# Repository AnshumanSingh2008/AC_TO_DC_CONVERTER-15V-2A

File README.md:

# 15 V / 2 A Linear DC Power Supply (LM350) - KiCad Design Study

A transformer-based, regulated 15 V / 2 A DC supply designed in KiCad as a learning project. The goal was to recreate a commercial plug-in AC-DC adapter. The design works on paper and passes ERC and DRC, but comparing it with the real adapter showed that a linear supply is the wrong architecture for a compact, low-cost product. This README documents the design and, more importantly, why it was not taken to fabrication.

## Project status

| Item | Status |
|---|---|
| Schematic | Complete, ERC clean |
| PCB layout | Complete, DRC clean |
| Gerbers and drill files | Generated (`fabrication/`) |
| Fabricated and tested | **No. Design only.** |
| Decision | Not fabricated, for cost and size reasons (see below) |

## Specifications

| Parameter | Value |
|---|---|
| Input | 18 V AC from an external 230 V isolating transformer (3 A secondary) |
| Output | 15 V DC, up to 2 A |
| Regulator | LM350 adjustable (TO-220) |
| Rectifier | Bridge of 4 x 1N5408 |
| Bulk filter | 4700 uF / 35 V |
| Board size | 71.1 mm x 63 mm, two layers |
| Connectors | 2 x 5.08 mm screw terminals (AC in, DC out) |

No mains voltage reaches the PCB. Mains connects only to the off-board transformer primary.

## How it works

```
230 V AC -> Transformer (off-board) -> 18 V AC -> J1
   -> Bridge rectifier (D5-D8) -> C1 bulk filter (~24 V DC peak)
   -> C2 input bypass -> U1 LM350 -> C3/C4 -> J2 (15 V out)
```

- **Bridge and C1** convert the 18 V AC to rippled DC of about 22-24 V.
- **U1 (LM350)** holds 1.25 V between its output and ADJ pins. R1 = 120 ohm and R2 = 1.3 kohm set the output: Vout = 1.25 x (1 + R2/R1), about 14.8 V.
- **D1** (output to input) and **D2** (ADJ to output) protect the regulator from capacitor discharge if the input collapses.
- **C2, C3, C4** provide input bypass, output stability and ADJ ripple reduction.
- **R3 + LED** give a power indicator.

## Key design decisions

| Decision | Reason |
|---|---|
| LM350 instead of 7815 | 78xx parts are limited to 1.5 A; 2 A needed an adjustable 3 A part |
| 1N5408 bridge diodes | 3 A rating; 1N4007 (1 A) is too small for 2 A with capacitor-input peaks |
| 18 V AC secondary | Gives enough headroom (about 3 V) above 15 V under load and mains dips |
| Off-board transformer | Keeps mains off the PCB, so no creepage/clearance issues and a safe board to handle |
| 2 mm tracks on power paths | Sized for 2 A on 1 oz copper; thin 0.5 mm tracks on mA-level signal nets |

## Why I did not build it (the learnings)

### 1. The PCB alone was larger than a commercial adapter

The commercial 12 V / 2 A adapter I wanted to match measures about **7.8 cm x 4.7 cm**, including its plastic case and mains pins. My bare PCB measures **7.1 cm x 6.3 cm**, before adding the transformer, heatsink and enclosure.

The reason is architecture, not layout quality:

- The adapter is a **switch-mode power supply (SMPS)**. It rectifies mains directly and switches at tens of kHz, so its transformer is a tiny ferrite part.
- My design is a **linear supply**. It needs a 50 Hz transformer (large and heavy), a 4700 uF bulk capacitor, large 1N5408 diodes, and a heatsink for the regulator.
- The LM350 dissipates roughly (Vin - Vout) x I, about 14 W or more at full load, so the regulator needs a large heatsink and ventilation.

### 2. The transformer alone cost more than the complete adapter

A suitable 18 V / 3 A isolating transformer costs about **Rs 1500**. The finished commercial adapter costs about **Rs 450**. Before counting the PCB, regulator, heatsink, capacitors, fuse and enclosure, the design is already several times more expensive than the product it was meant to replace.

### Conclusion

For a compact, low-cost 12-15 V / 2 A adapter, a linear supply is the wrong choice. A **flyback SMPS** is the right architecture: smaller, cooler, and cheaper. A linear design still makes sense where low noise matters more than size and cost, such as a bench supply or an analogue project.

## Skills practised

- Schematic capture and ERC (including `PWR_FLAG` for power-input errors)
- Selecting footprints from datasheet dimensions (and catching wrong default footprints)
- Adjustable regulator design and protection diode orientation
- Net classes and trace widths sized to current
- Two-layer routing, vias and copper pours
- Reading DRC: clearance, shorting and unconnected-item violations
- Gerber, drill, BOM and PDF output
- Engineering trade-off analysis: linear vs switch-mode, cost, size and efficiency

## Repository structure

```
hardware/       KiCad project (.kicad_pro, .kicad_sch, .kicad_pcb)
DOCS/           Schematic PDF, PCB layout PDF, IMAGES, notes
fabrication/    Gerbers, drill files, zip
```

## Safety note

The transformer primary is connected to mains (230 V) and is dangerous. Anyone building this must use an enclosed, isolating transformer, a fuse on the primary side, and insulated wiring. The PCB itself carries only about 18 V AC and 15-24 V DC.

An earlier iteration of this project connected a rectifier directly to mains with no isolation. That approach was abandoned because it produces about 325 V DC that is live relative to earth and cannot give 12-15 V.

## Possible next steps

- Study and design a flyback SMPS (controller IC, ferrite transformer, optocoupler feedback)
- Build a smaller low-voltage project (for example 5 V regulator or sensor board) that can actually be fabricated and tested

## License

No license is specified. All rights are reserved by the author. This repository is shared for viewing and learning.

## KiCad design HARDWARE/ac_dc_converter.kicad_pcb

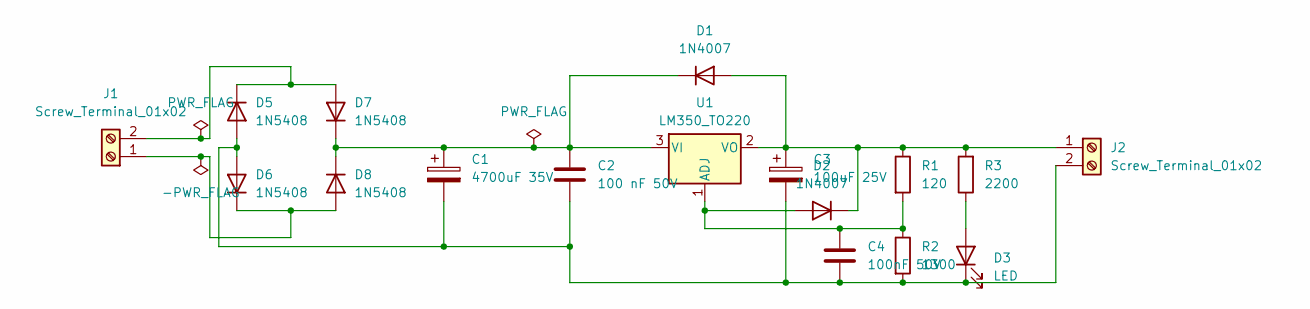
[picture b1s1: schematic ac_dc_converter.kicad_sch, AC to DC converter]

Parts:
C1: 4700uF 35V; CP_Radial_D16.0mm_P7.50mm
C2: 100 nF 50V; C_Disc_D7.0mm_W2.5mm_P5.00mm
C3: 100uF 25V; CP_Radial_D6.3mm_P2.50mm
C4: 100nF 50V; C_Disc_D7.0mm_W2.5mm_P5.00mm
D1, D2: 1N4007; D_DO-41_SOD81_P10.16mm_Horizontal
D3: LED; LED_D5.0mm
D5, D6, D7, D8: 1N5408; D_DO-201AD_P15.24mm_Horizontal
J1, J2: Screw_Terminal_01x02; TerminalBlock_CUI_TB007-508-02_1x02_P5.08mm_Horizontal
R1: 120; R_Axial_DIN0207_L6.3mm_D2.5mm_P7.62mm_Horizontal
R2: 1300; R_Axial_DIN0207_L6.3mm_D2.5mm_P7.62mm_Horizontal
R3: 2200; R_Axial_DIN0207_L6.3mm_D2.5mm_P7.62mm_Horizontal
U1: LM350_TO220; TO-220-3_Vertical

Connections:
unnamed: C3.1, D1.2 (A), D2.1 (K), J2.1, R1.1, R3.2, U1.2 (VO)
unnamed: C1.1, C2.1, D1.1 (K), D7.1 (K), D8.1 (K), U1.3 (VI)
unnamed: C4.1, D2.2 (A), R1.2, R2.1, U1.1 (ADJ)
unnamed: D3.2 (A), R3.1
unnamed: C1.2, C2.2, C3.2, C4.2, D3.1 (K), D5.2 (A), D6.2 (A), J2.2, R2.2
unnamed: D5.1 (K), D7.2 (A), J1.2
unnamed: D6.1 (K), D8.2 (A), J1.1

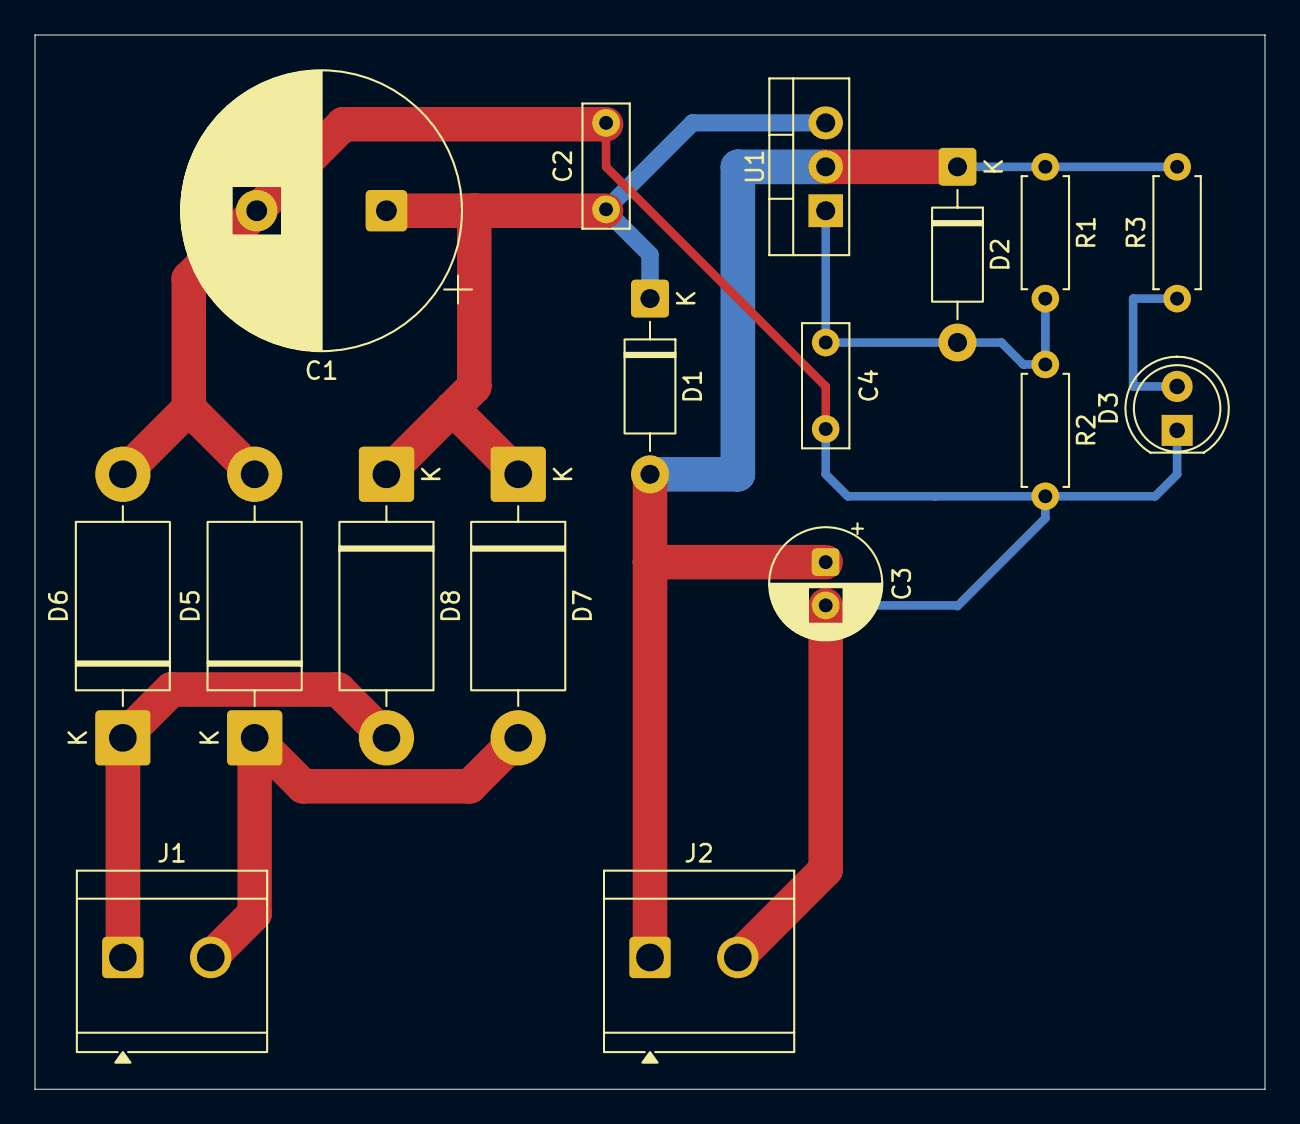
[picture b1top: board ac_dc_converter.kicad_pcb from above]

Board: 2 copper layers, 71.1 x 61.0 mm, 17 parts (0 on the bottom side), 7 nets.
